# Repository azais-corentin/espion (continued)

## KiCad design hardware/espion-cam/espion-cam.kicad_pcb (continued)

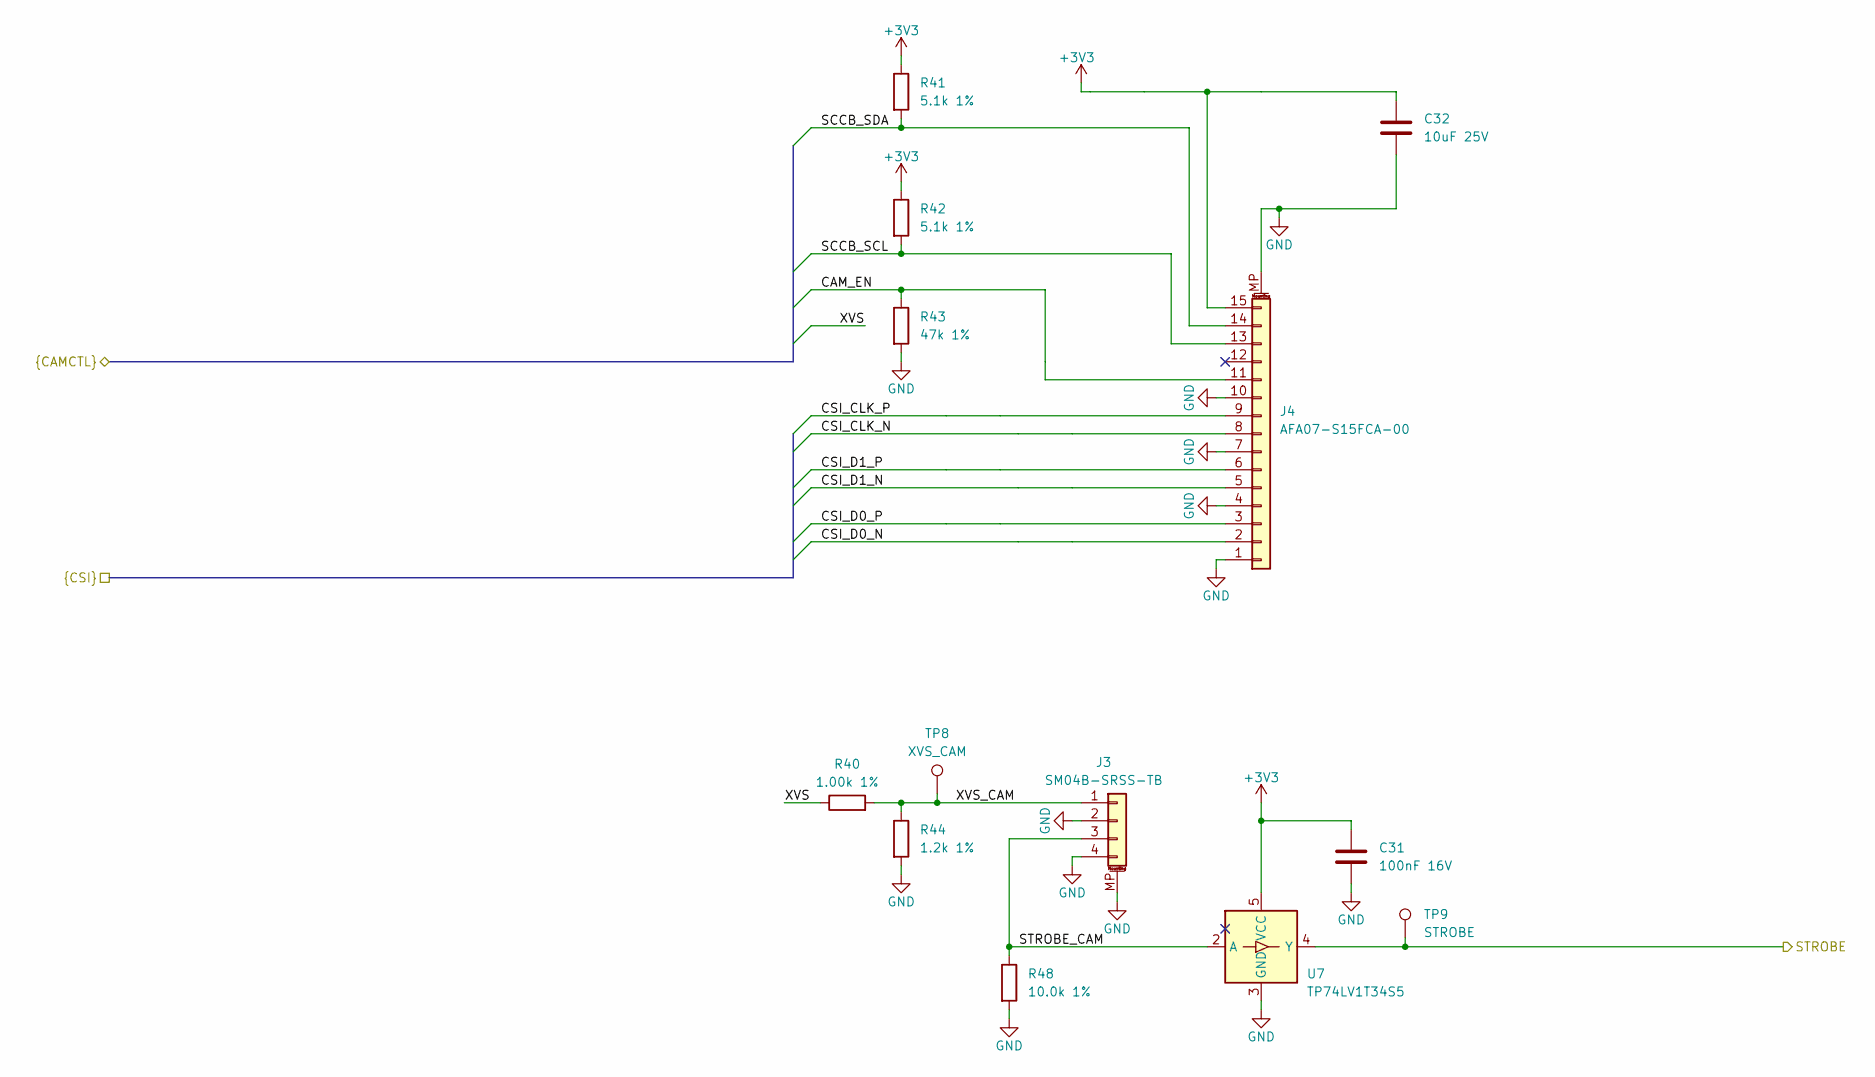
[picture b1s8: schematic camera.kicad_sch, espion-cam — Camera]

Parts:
C31: 100nF 16V; C_0402_1005Metric; MPN CL05B104KO5NNNC; LCSC C1525
C32: 10uF 25V; C_0805_2012Metric; MPN CL21A106KAYNNNE; LCSC C15850
J3: SM04B-SRSS-TB; JST_SH_SM04B-SRSS-TB_1x04-1MP_P1.00mm_Horizontal; MPN SM04B-SRSS-TB(LF)(SN); LCSC C160404
J4: AFA07-S15FCA-00; JUSHUO_AFA07-S15FCA-00_1x15-1MP_P1.0mm_Horizontal; MPN AFA07-S15FCA-00; LCSC C262721
R40: 1.00k 1%; R_0402_1005Metric; MPN 0402WGF1001TCE; LCSC C11702
R41, R42: 5.1k 1%; R_0402_1005Metric; MPN 0402WGF5101TCE; LCSC C25905
R43: 47k 1%; R_0402_1005Metric; MPN 0402WGF4702TCE; LCSC C25792
R44: 1.2k 1%; R_0402_1005Metric; MPN 0402WGF1201TCE; LCSC C25862
R48: 10.0k 1%; R_0402_1005Metric; MPN 0402WGF1002TCE; LCSC C25744
TP8: XVS_CAM; TestPoint_Pad_D1.0mm
TP9: STROBE; TestPoint_Pad_D1.0mm
U7: TP74LV1T34S5; SOT-23-5; MPN TP74LV1T34S5; LCSC C47117591

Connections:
+3V3: C31.1, C32.1, J4.15, R41.1, R42.1, U7.5 (VCC); also elsewhere on the board
/Camera/CAM_EN: J4.11, R43.1; also elsewhere on the board
/Camera/CSI_CLK_N: J4.8; also elsewhere on the board
/Camera/CSI_CLK_P: J4.9; also elsewhere on the board
/Camera/CSI_D0_N: J4.2; also elsewhere on the board
/Camera/CSI_D0_P: J4.3; also elsewhere on the board
/Camera/CSI_D1_N: J4.5; also elsewhere on the board
/Camera/CSI_D1_P: J4.6; also elsewhere on the board
/Camera/SCCB_SCL: J4.13, R42.2; also elsewhere on the board
/Camera/SCCB_SDA: J4.14, R41.2; also elsewhere on the board
/Camera/STROBE: TP9.1 (1_1), U7.4 (Y); also elsewhere on the board
/Camera/STROBE_CAM: J3.3, R48.1, U7.2 (A)
/Camera/XVS: R40.1; also elsewhere on the board
/Camera/XVS_CAM: J3.1, R40.2, R44.1, TP8.1 (1_1)
GND: C31.2, C32.2, J3.2, J3.4, J3.MP (MountPin), J4.1, J4.4, J4.7, J4.10, J4.MP (MountPin), R43.2, R44.2, R48.2, U7.3 (GND); also elsewhere on the board

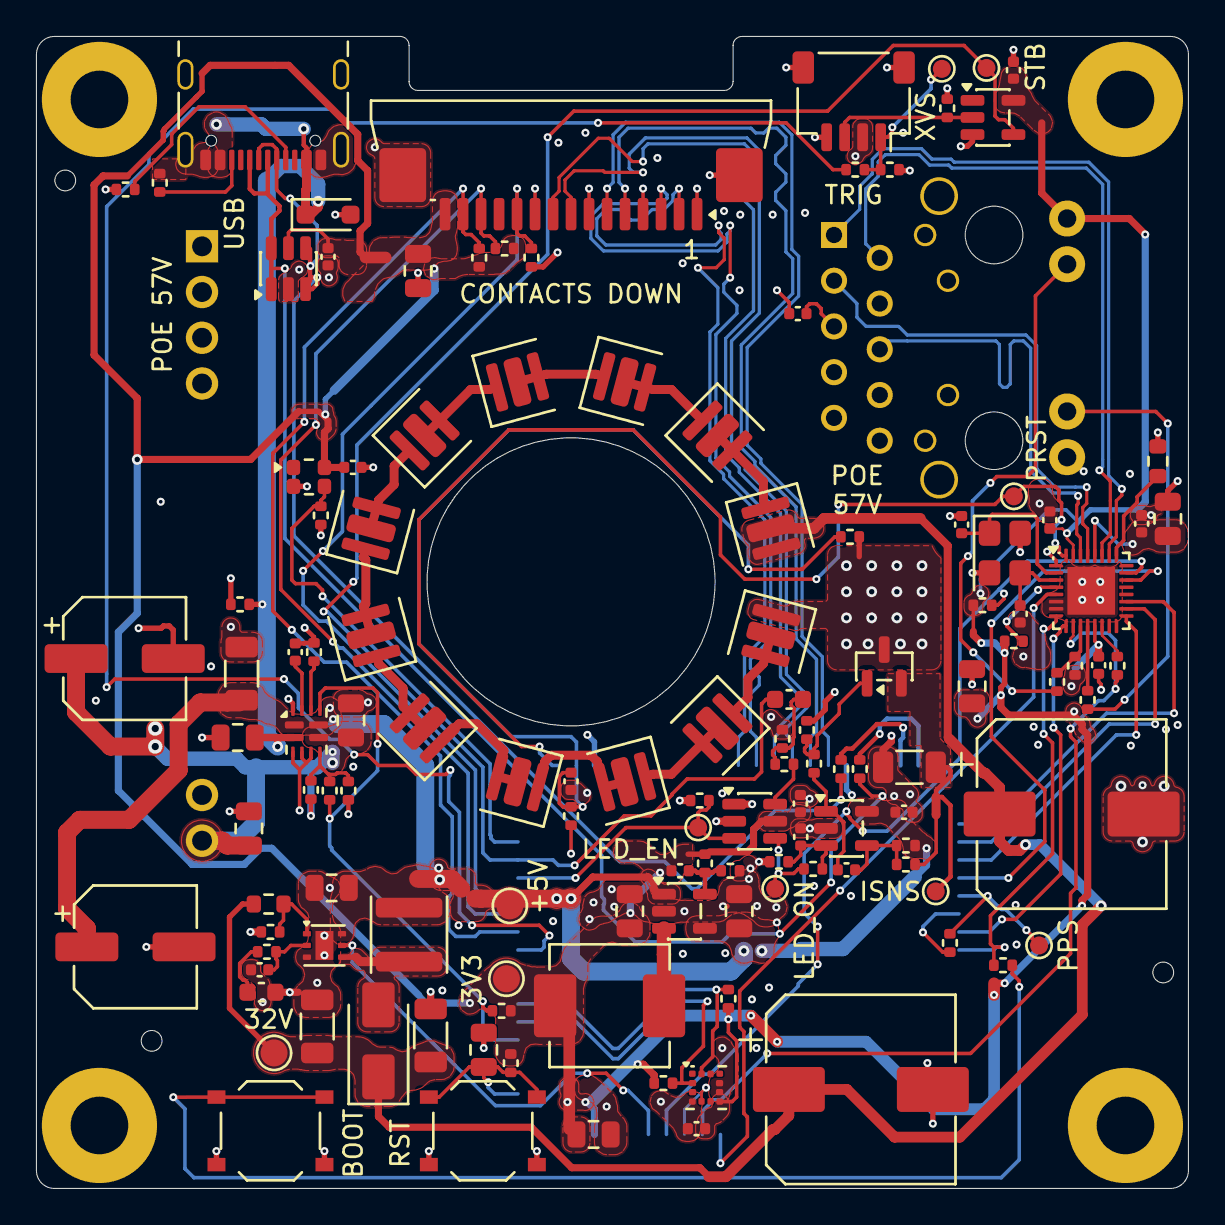
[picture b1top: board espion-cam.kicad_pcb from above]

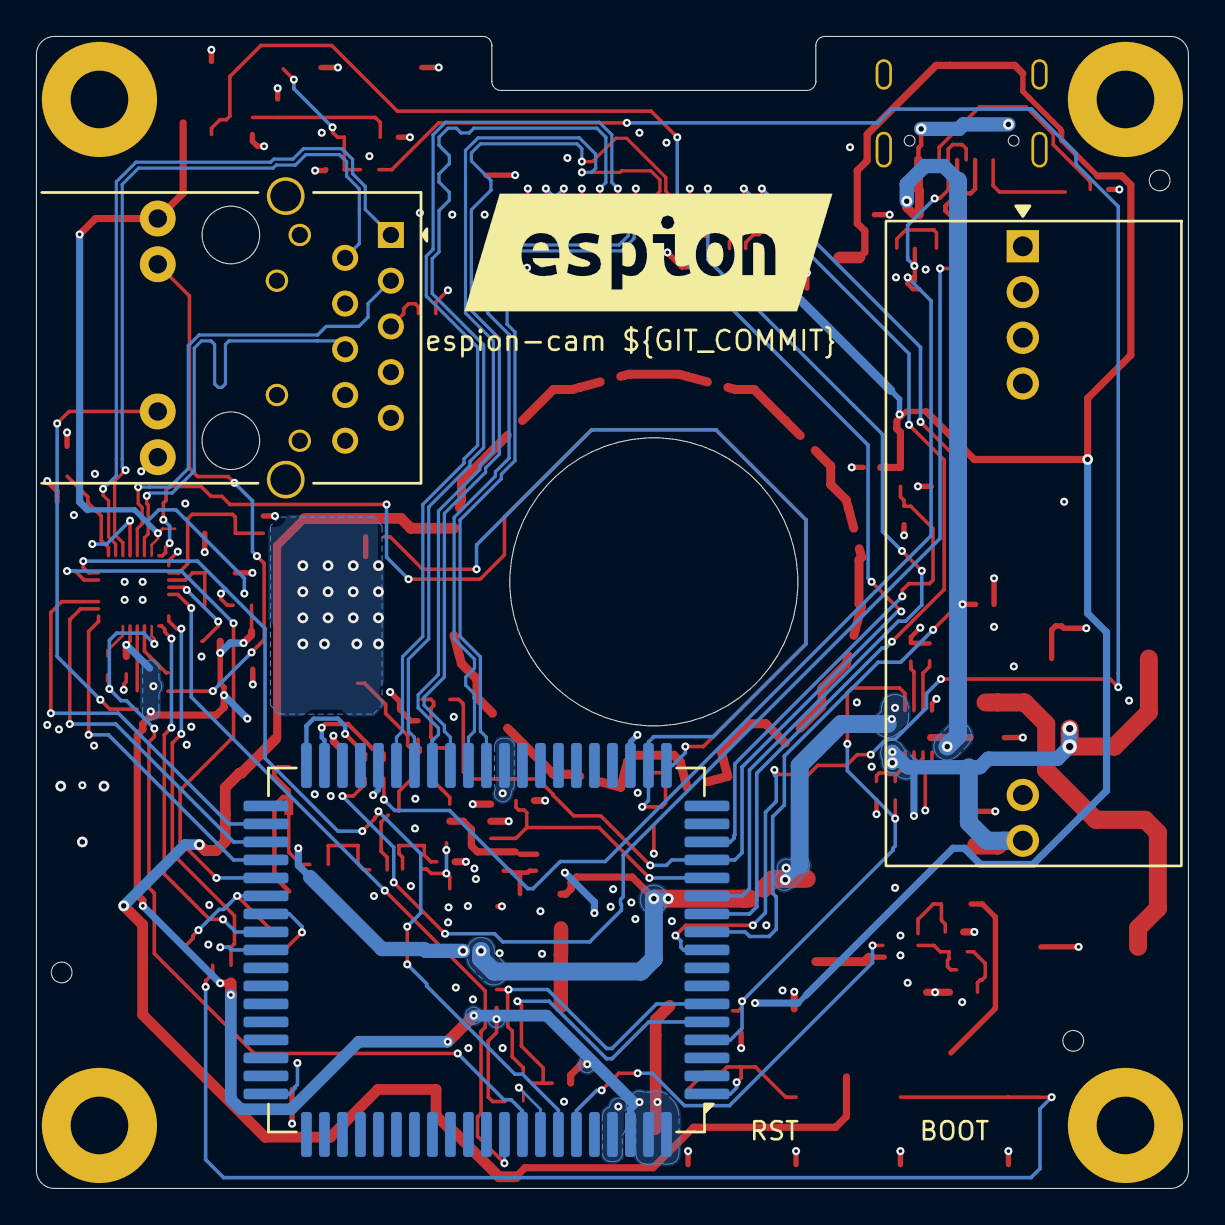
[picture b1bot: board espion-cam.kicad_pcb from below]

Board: 4 copper layers, 64.0 x 64.0 mm, 139 parts (4 on the bottom side), 96 nets.

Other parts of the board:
TOOL1, TOOL2, TOOL3: ToolingHole_1.152mm_JLCPCB
kibuzzard-6AFF7ADE: G***; kibuzzard-6AFF7ADE

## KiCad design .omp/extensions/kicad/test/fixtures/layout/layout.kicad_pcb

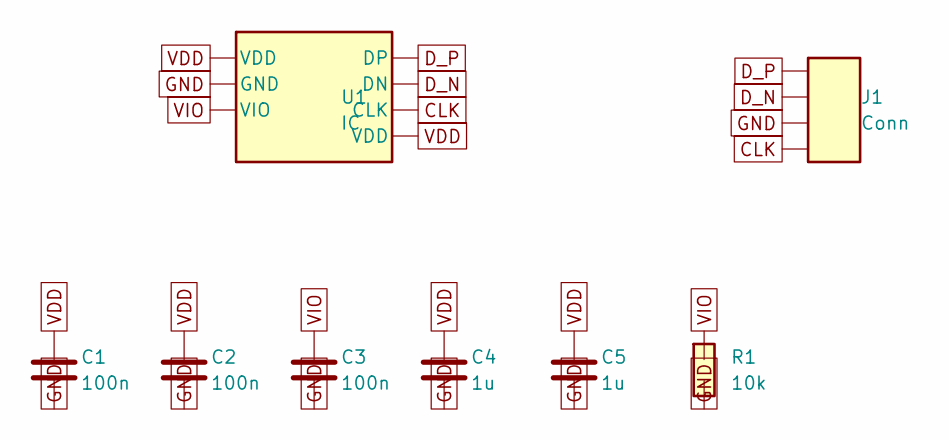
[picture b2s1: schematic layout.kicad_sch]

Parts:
C1, C2, C3: 100n; C
C4, C5: 1u; C
J1: Conn; J
R1: 10k; R
U1: IC

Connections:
CLK: J1.4, U1.6 (CLK)
D_N: J1.2, U1.5 (DN)
D_P: J1.1, U1.4 (DP)
GND: C1.2, C2.2, C3.2, C4.2, C5.2, J1.3, R1.2, U1.2 (GND)
VDD: C1.1, C2.1, C4.1, C5.1, U1.1 (VDD), U1.7 (VDD)
VIO: C3.1, R1.1, U1.3 (VIO)

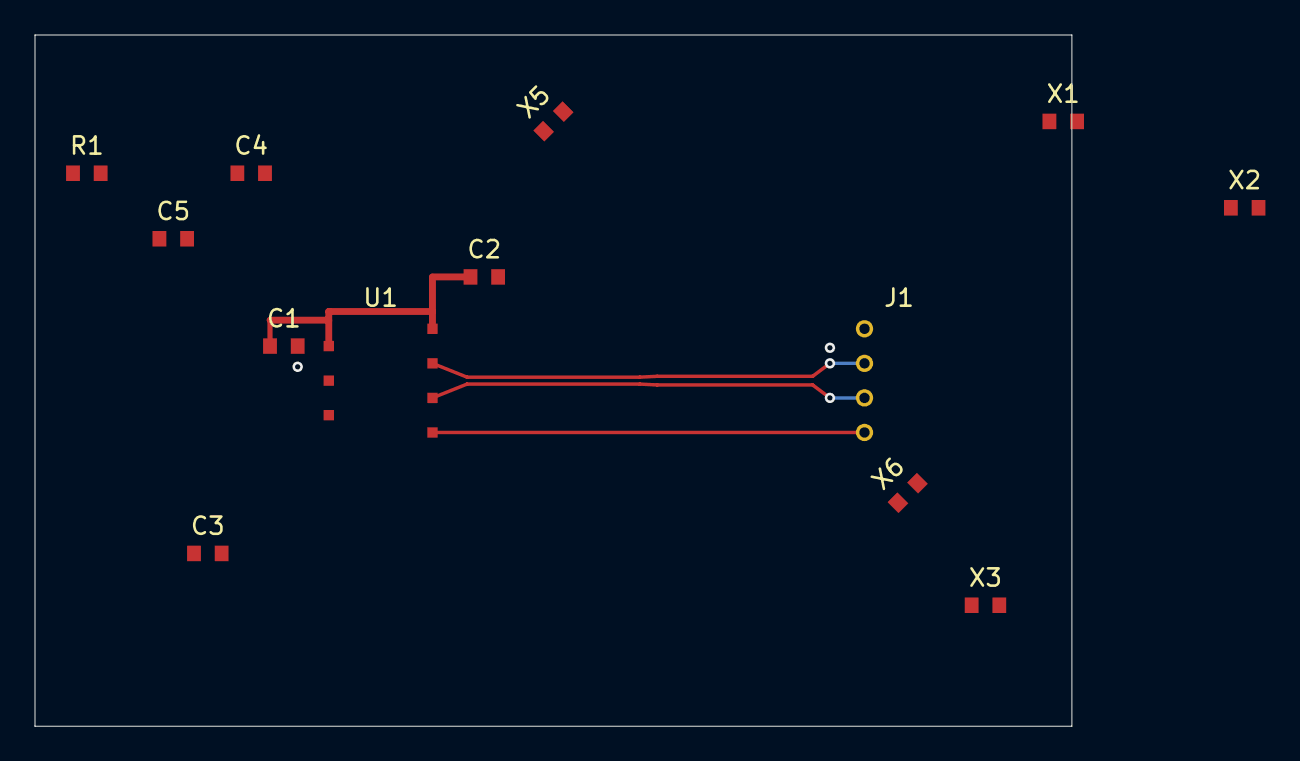
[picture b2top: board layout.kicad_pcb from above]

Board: 4 copper layers, 60.0 x 40.0 mm, 14 parts (1 on the bottom side), 6 nets.

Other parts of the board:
X1: edge; C
X2: off; C
X3: keepout; C
X4: bottom; C
X5, X6: rotated; C

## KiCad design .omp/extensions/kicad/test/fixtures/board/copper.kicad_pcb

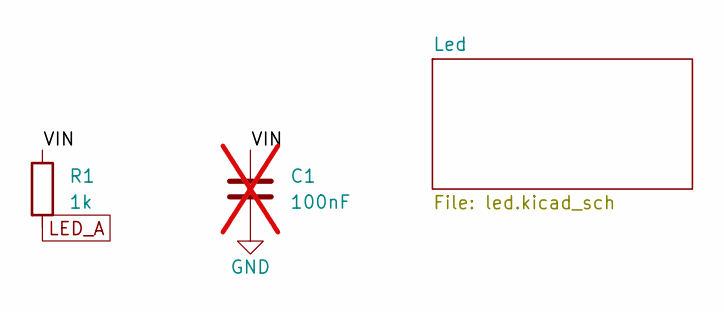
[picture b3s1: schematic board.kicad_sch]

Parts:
C1: 100nF; C_0603_1608Metric; MPN CC0603KRX7R9BB104; LCSC C14663; not fitted
R1: 1k; R_0603_1608Metric; MPN 0603WAF1001T5E; LCSC C21190

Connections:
/VIN: C1.1, R1.1
GND: C1.2; also elsewhere on the board
LED_A: R1.2; also elsewhere on the board

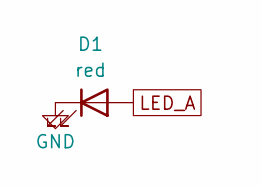
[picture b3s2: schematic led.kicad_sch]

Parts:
D1: red; LED_Fixture_0603; MPN 19-217/R6C-AL1M2VY/3T; LCSC C72044

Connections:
GND: D1.1 (K); also elsewhere on the board
LED_A: D1.2 (A); also elsewhere on the board

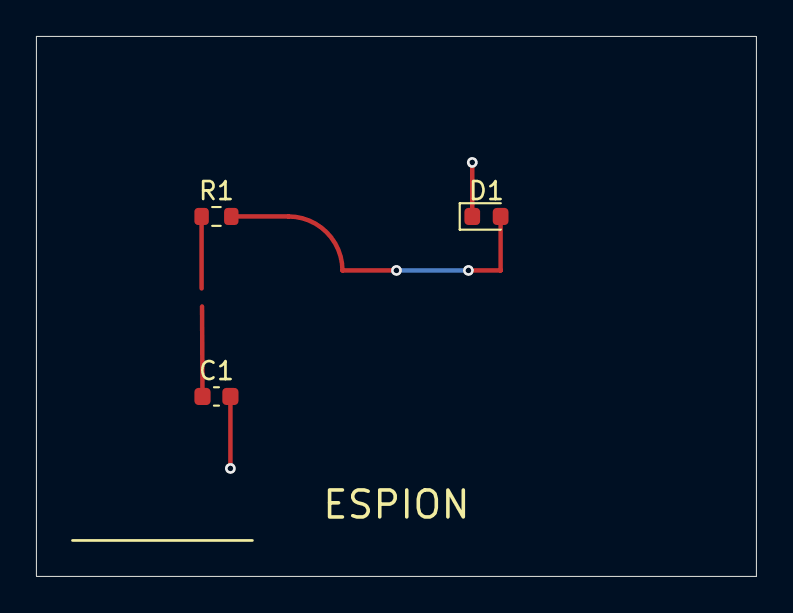
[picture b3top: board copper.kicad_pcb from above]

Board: 2 copper layers, 40.0 x 30.0 mm, 3 parts (0 on the bottom side), 3 nets.

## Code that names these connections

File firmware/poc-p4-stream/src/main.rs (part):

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//!
//! Board facts (Waveshare `ESP32-P4-ETH-datasheet.pdf`, the schematic, sheet 1):
//! - UART0 to the CH343P USB-UART bridge (U4): P4 GPIO37 = U0TXD -> CH343 RXD, CH343 TXD ->
//!   GPIO38 = U0RXD. CH343 RTS/DTR drive EN and GPIO35 (BOOT) through U5 for auto-reset.
//! - Ethernet: IP101GRI PHY U10 on RMII; pins in `net`.
//! - Camera: CSI connector J1, SCCB on GPIO7/GPIO8; set-up in `camera`.

#![no_std]
#![no_main]
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
    let pins = net::Pins {
        eth: p.ETH,
        ref_clk: p.GPIO50,
        rxd0: p.GPIO29,
        rxd1: p.GPIO30,
        crs_dv: p.GPIO28,
        txd0: p.GPIO34,
        txd1: p.GPIO35,
        tx_en: p.GPIO49,
        mdc: p.GPIO31,
        mdio: p.GPIO52,
    };
    let stack = net::start(spawner, pins, p.GPIO51).await;
    match (SERVICE, stack, psram) {
        (Service::Bench | Service::BenchVision, Some(stack), Some(psram)) => {
            let (frames, psram) = psram.split_at_mut(camera::BUFFERS * camera::BUFFER_LEN);
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
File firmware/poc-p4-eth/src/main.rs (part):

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//!
//! Board facts (Waveshare `ESP32-P4-ETH-datasheet.pdf`, the schematic, sheet 1):
//! - UART0 to the CH343P USB-UART bridge (U4): P4 GPIO37 = U0TXD -> CH343 RXD, CH343 TXD ->
//!   GPIO38 = U0RXD. CH343 RTS/DTR drive EN and GPIO35 (BOOT) through U5 for auto-reset.
//! - CSI connector J1 (22 pin, Pi 5 pinout): pin 2 ESP_I2C_SDA, pin 3 ESP_I2C_SCL (2.2 k
//!   pull-ups R46/R44 to 3.3 V; the bus is shared with the ES8311 codec), pin 6 CSI_IO0
//!   (10 k R42 to 3.3 V, no GPIO), pin 5 CSI_IO1 (pull-up R43 not fitted, no GPIO).
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// The benchmark's 300 KiB frame buffer and the strip ring do not both fit in internal RAM.
const _: () = assert!(!(RUN_BENCH && (PLAN.strips.is_some() || RUN_CORE1)));

/// SCCB data: net ESP_I2C_SDA, U6 pin 7 (GPIO7) to CSI connector J1 pin 2.
const SCCB_SDA_GPIO: u8 = 7;
/// SCCB clock: net ESP_I2C_SCL, U6 pin 8 (GPIO8) to CSI connector J1 pin 3.
const SCCB_SCL_GPIO: u8 = 8;
/// SCCB clock rate.
const SCCB_FREQ_KHZ: u32 = 100;
/// Camera enable (J1 pin 6, CSI_IO0, the module's PWDN pin on the 15-pin side): not wired to
/// a GPIO on this board. R42 (10 k) holds it at 3.3 V.
const CAM_EN_GPIO: Option<u8> = None;
/// OV9281 SCCB addresses tried, in order: datasheet write addresses 0xC0 and 0x20 (7-bit 0x60
/// and 0x10). The module on the bench answers at 0x60 (and also at 0x70 with the same chip ID).
const OV9281_ADDRESSES: [Address; 2] = [Address::Primary, Address::Alternate];
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        I2cConfig::default().with_frequency(Rate::from_khz(SCCB_FREQ_KHZ)),
    )
    .expect("I2C0 config")
    // SAFETY: GPIO7/GPIO8 are used only by this bus.
    .with_sda(unsafe { AnyPin::steal(SCCB_SDA_GPIO) })
    .with_scl(unsafe { AnyPin::steal(SCCB_SCL_GPIO) })
    .into_async();
    info!(
        "SCCB: I2C0 SDA GPIO{SCCB_SDA_GPIO} SCL GPIO{SCCB_SCL_GPIO} {SCCB_FREQ_KHZ} kHz, camera enable {}",
        match CAM_EN_GPIO {
            Some(_) => "on a GPIO",
            None => "hard-wired high (R42)",
        }
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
